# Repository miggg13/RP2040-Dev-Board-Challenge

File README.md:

README

RP2040 12key 

A 12 key keyboard using a Raspberry Pi Pico which is powered by RP2040 microchip. Made for the Bronco Space PCB Design Hackathon. 
This small 12 key macropod can be used for shortcuts such as the function keys or media control. 

COMPONENTS 

1x Raspberry Pico W 

12x Keyboard Switches 

12x 1N4148W Diodes (surface mount) 

12x Keycaps 

1x PCB 

BOARD 

PCB dimensions are 100mmx100mm

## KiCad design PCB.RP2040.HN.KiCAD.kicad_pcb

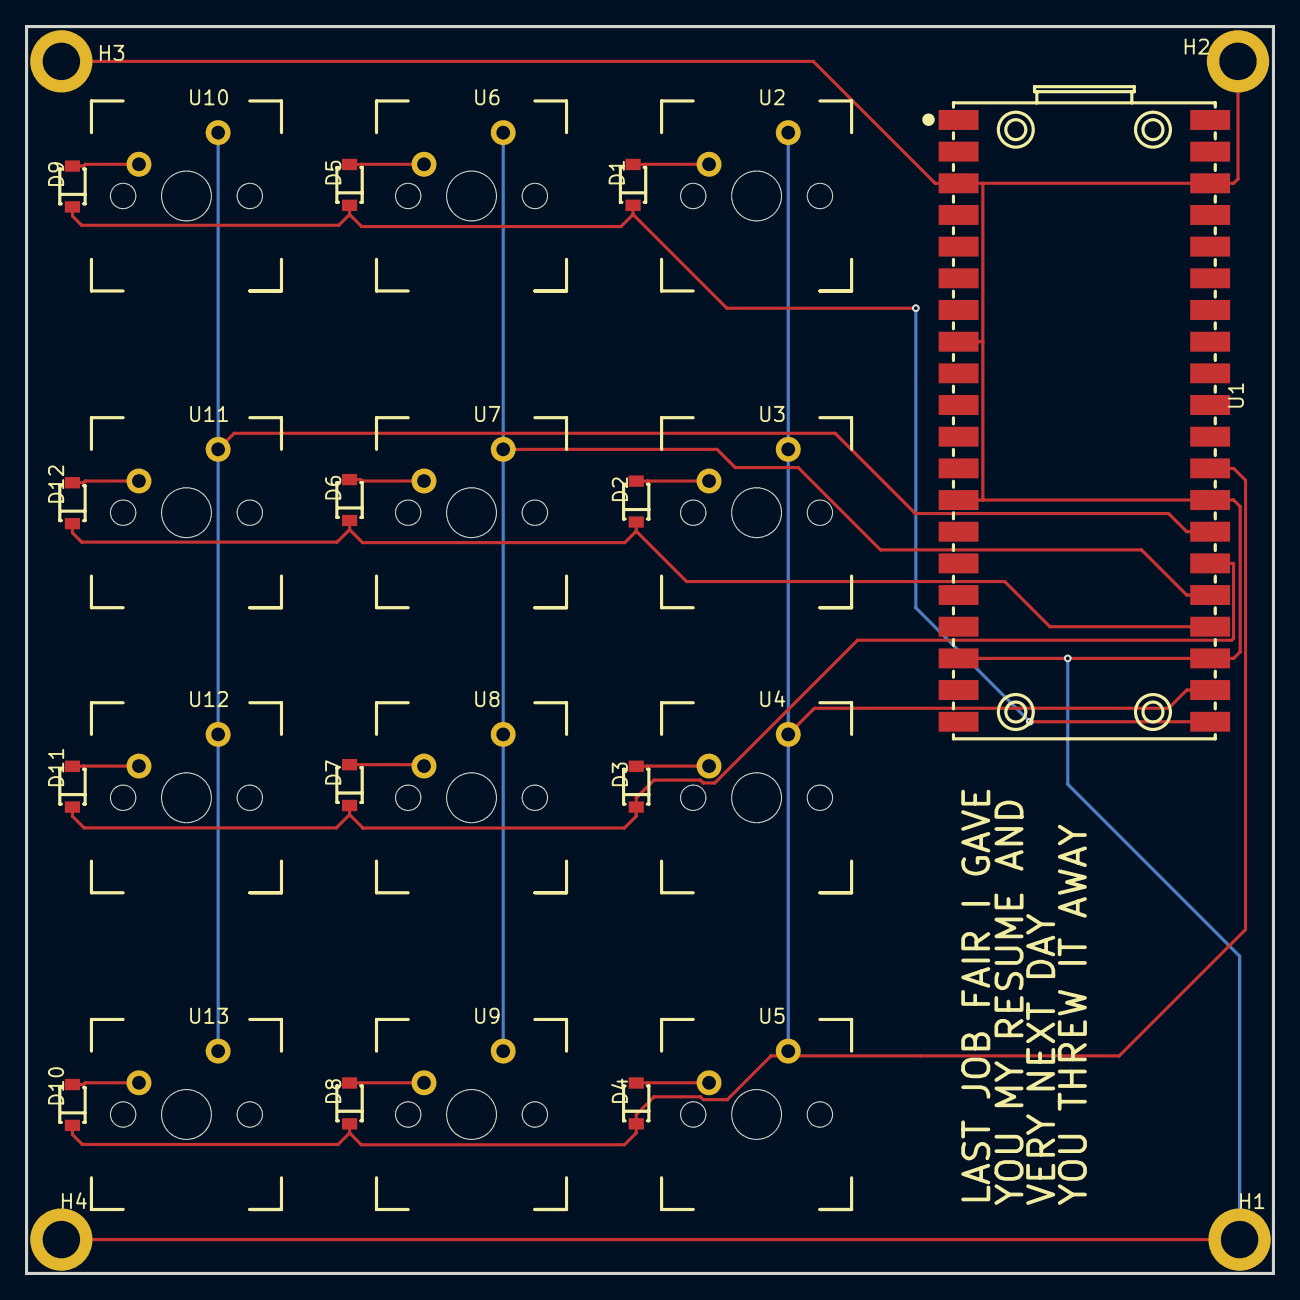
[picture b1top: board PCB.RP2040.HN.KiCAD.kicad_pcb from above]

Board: 2 copper layers, 100.0 x 100.0 mm, 29 parts (0 on the bottom side), 20 nets.

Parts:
D1, D2, D3, D4, D5, D6, D7, D8, D9, D10, D11, D12: 1N4148W-7-F; 1N4148W-7-F_FOOTPRINT
H1, H2, H3, H4: 3MMHOLE; 3MMHOLE_PTH
U1: PICO W; LCC-40_L51.0-W21.0-P2.54-BL_RP2040-BASED
U2, U3, U4, U5, U6, U7, U8, U9, U10, U11, U12, U13: MK; MECHANICAL KEYSWITCH FOORPRINT

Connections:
GND: H1.1, H2.1, H3.1, H4.1, U1.3, U1.8, U1.13, U1.18, U1.23, U1.28, U1.38
GP16: D1.1, D5.1, D9.1, U1.21
GP17: U1.22, U2.1, U3.1, U4.1, U5.1
GP18: D2.1, D6.1, D12.1, U1.24
GP19: U1.25, U6.1, U7.1, U8.1, U9.1
GP20: D3.1, D7.1, D11.1, U1.26
GP21: U1.27, U10.1, U11.1, U12.1, U13.1
GP22: D4.1, D8.1, D10.1, U1.29
U2_2: D1.2, U2.2
U3_2: D2.2, U3.2
U4_2: D3.2, U4.2
U5_2: D4.2, U5.2
U6_2: D5.2, U6.2
U7_2: D6.2, U7.2
U8_2: D7.2, U8.2
U9_2: D8.2, U9.2
U10_2: D9.2, U10.2
U11_2: D12.2, U11.2
U12_2: D11.2, U12.2
U13_2: D10.2, U13.2
